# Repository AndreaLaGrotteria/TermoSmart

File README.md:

# TermoSmart

Progetto per un termostato smart connesso a Internet con un modulo NodeMCU. La repository contiene anche il codice per il server node.js e le schematiche per la board.

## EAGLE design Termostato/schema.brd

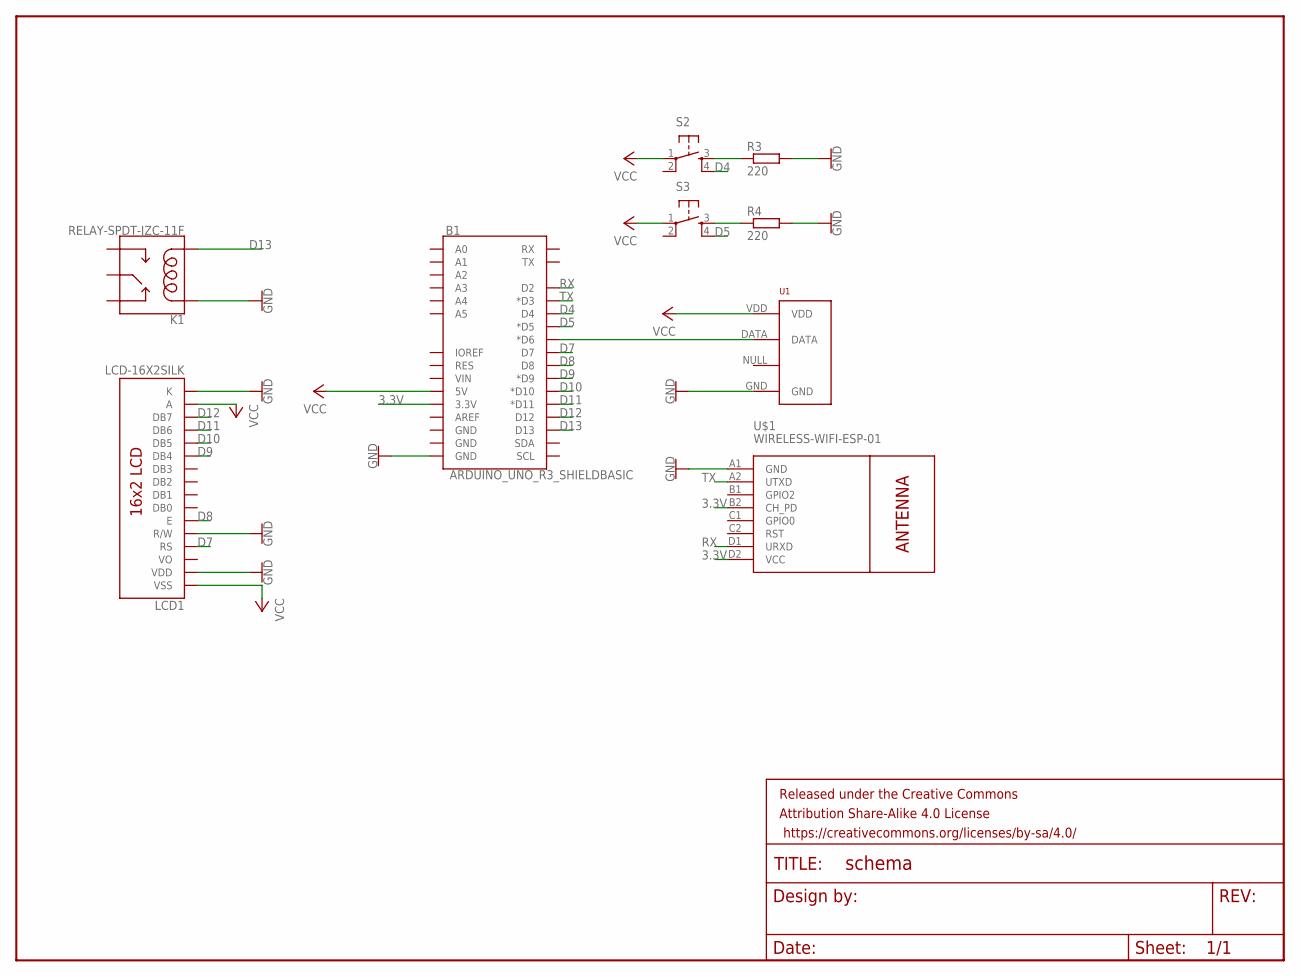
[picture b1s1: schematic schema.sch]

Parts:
B1: ARDUINO_UNO_R3_SHIELDBASIC; UNO_R3_SHIELD
FRAME1: FRAME-LETTER; CREATIVE_COMMONS
K1: RELAY-SPDT-JZC-11F; RELAY-JZC
LCD1: LCD-16X2SILK; LCD-16X2
R3, R4: 220; 0204/7
S2, S3: TAC_SWITCHPTH; TACTILE-PTH
U1: RHT03_DHT-22_AM2302RA; RHT03_DHT-22/RA
U$1: WIRELESS-WIFI-ESP-01

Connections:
3.3V: B1.3.3V, U$1.B2 (CH_PD), U$1.D2 (VCC)
D4: B1.D4, S2.4
D5: B1.D5 (*D5), S3.4
D7: B1.D7, LCD1.4 (RS)
D8: B1.D8, LCD1.6 (E)
D9: B1.D9 (*D9), LCD1.11 (DB4)
D10: B1.D10 (*D10), LCD1.12 (DB5)
D11: B1.D11 (*D11), LCD1.13 (DB6)
D12: B1.D12, LCD1.14 (DB7)
D13: B1.D13, K1.1 (COIL2)
GND: B1.GND@0 (GND), K1.5 (COIL1), LCD1.2 (VDD), LCD1.5 (R/W), LCD1.16 (K), R3.2, R4.2, U1.GND, U$1.A1 (GND)
unnamed: R3.1, S2.3
unnamed: B1.D6 (*D6), U1.DATA
unnamed: R4.1, S3.3
RX: B1.D2, U$1.D1 (URXD)
TX: B1.D3 (*D3), U$1.A2 (UTXD)
VCC: B1.5V, LCD1.1 (VSS), LCD1.15 (A), S2.1, U1.VDD

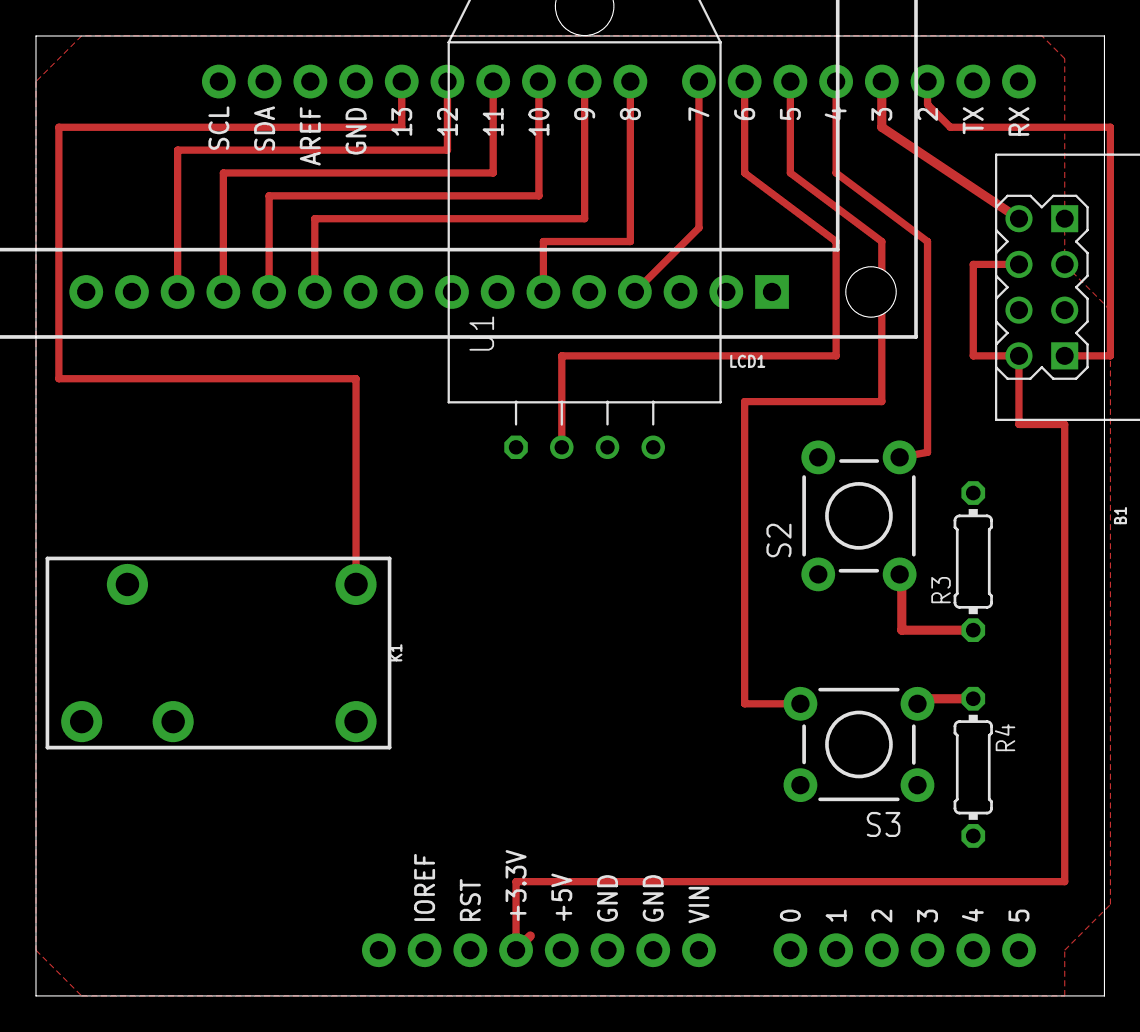
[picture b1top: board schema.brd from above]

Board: 2 copper layers, 59.4 x 53.3 mm, 10 parts (0 on the bottom side), 17 nets.

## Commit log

2017-10-17 Add files
2017-10-19 unfinished pinMap
2017-10-19 unfinished V1.1
2017-10-19 Add code for physical buttons, bug fix
2017-10-21 Electric scheme V1
2017-10-21 Removed backup files
2017-10-21 PCB design
2017-10-22 Add code for LCD, bug fix
2017-10-22 Spelling fix
2017-10-24 Add updating frequency for DHT11, bug fix
2017-10-27 Updated schematics V1.1
2017-10-27 Updated schematic
2017-10-27 Updated scematic
2017-10-29 Updated pinMap
2017-10-31 Arduino shield
2017-11-02 Update schematics: add 3.3V connection and switch from VIN to 5V
2017-11-03 Switch from SimpleDHT library to DHT_sensor_library
2017-11-23 Updated board design
2017-11-24 update arduino sketch with code for dht22
2018-01-23 update with code for nodeMCU, server and new schematics
2018-01-23 change server folder name
2018-01-23 cleaned schematcs directories
2018-01-23 bug fix
2018-01-23 Increased line width
2018-01-23 Increased route width

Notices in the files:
parts and their libraries:
SparkFun-Aesthetics: Licensing: Creative Commons ShareAlike 4.0 International - https://creativecommons.org/licenses/by-sa/4.0
SparkFun-Aesthetics: Released under the Creative Commons Attribution Share-Alike 4.0 License
SparkFun-Aesthetics: https://creativecommons.org/licenses/by-sa/4.0
